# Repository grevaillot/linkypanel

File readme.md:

# linky2ble epaper panel

## Preview:

## Schematics:

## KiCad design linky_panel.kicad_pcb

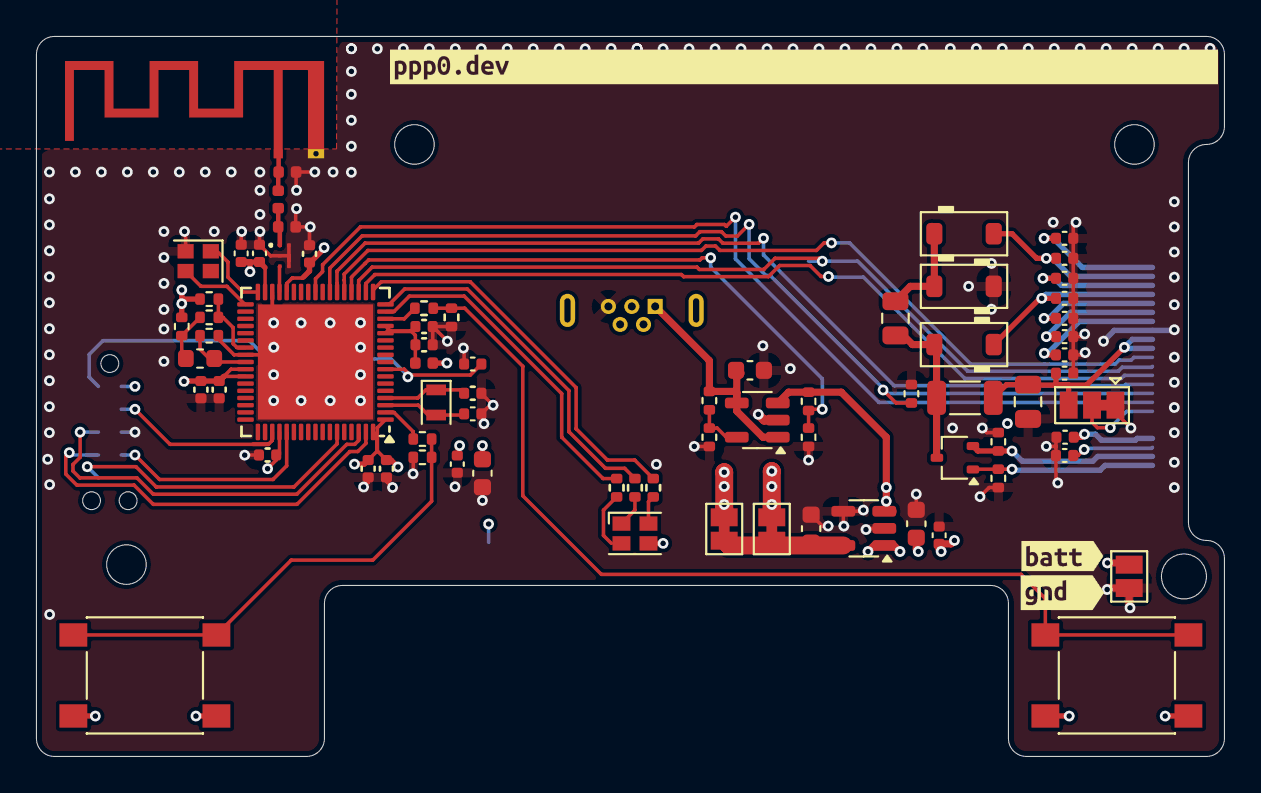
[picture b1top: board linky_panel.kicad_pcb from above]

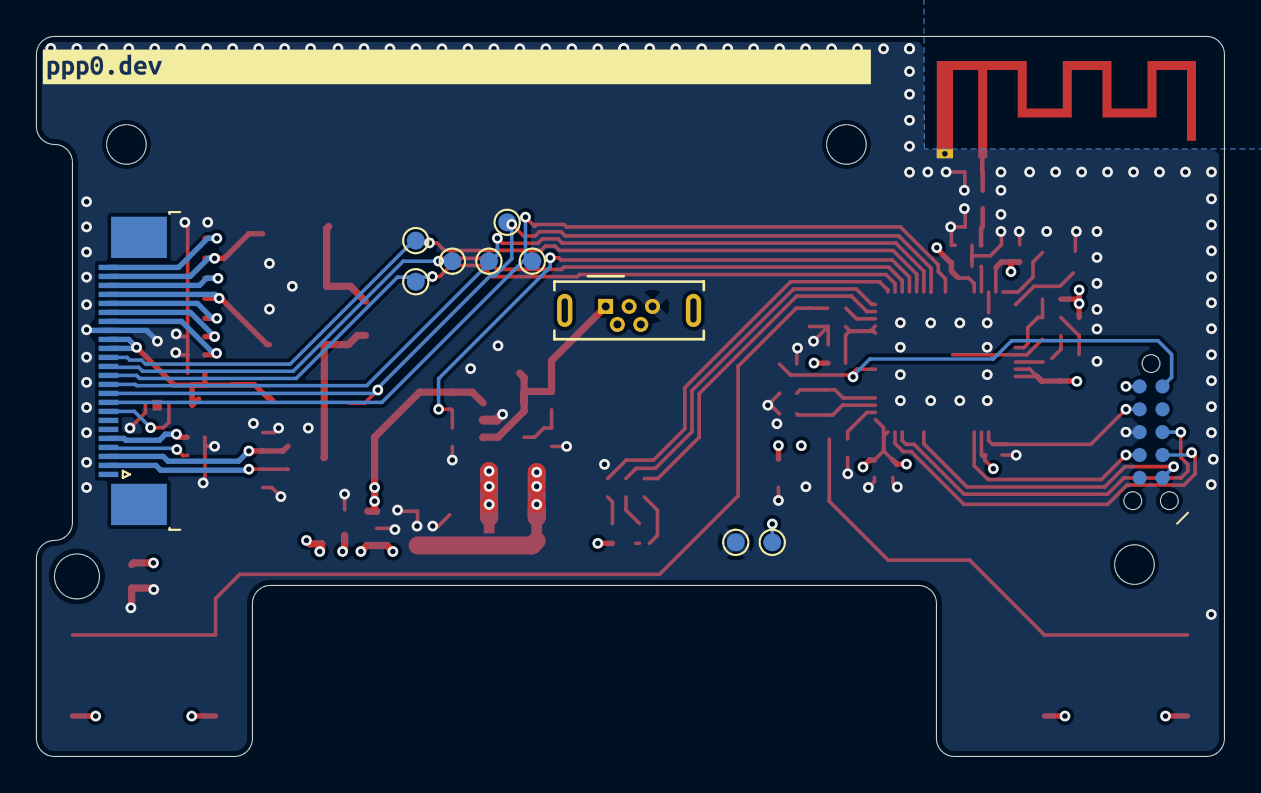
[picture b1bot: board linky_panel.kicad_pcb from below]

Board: 4 copper layers, 66.0 x 40.0 mm, 91 parts (12 on the bottom side), 55 nets.

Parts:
AE2: MLPF-WB55-01E3
AE3: Antenna; Texas_SWRA117D_2.4GHz_Left
C1, C2, C17, C33: 4.7uF; C_0603_1608Metric
C3, C5, C6, C9, C10, C11, C12, C13, C14, C16, C18, C27: 100nF; C_0402_1005Metric
C4: 100pF; C_0402_1005Metric
C7, C8: 10pF; C_0402_1005Metric
C15: 10nF; C_0402_1005Metric
C19, C20, C21, C22, C23, C24, C25, C28: 1uF; C_0402_1005Metric
C26: 1uF 25v; C_0402_1005Metric
C29, C30: 4.7uF 50V; C_0805_2012Metric
D1, D2, D3: MBR0530; D_SOD-123
D6: LED_RBAG; LED_Cree-PLCC4_2x2mm_CW
H1, H2, H2#2: MountingHole; MountingHole_2.2mm_M2
J1: Conn_01x24; TE_2-1734839-4_1x24-1MP_P0.5mm_Horizontal
J2: Conn_02x05_Counter_Clockwise; Tag-Connect_TC2050-IDC-NL_2x05_P1.27mm_Vertical
J3: USB_B_Micro; USB_Micro-B_Wuerth_614105150721_Vertical
J4: Conn_01x02_Pin; SolderJumper-2_P1.3mm_Open_Pad1.0x1.5mm
JP1: SolderJumper_3_Bridged123; SolderJumper-3_P1.3mm_Bridged12_Pad1.0x1.5mm
JP2, JP3: SolderJumper_2_Bridged; SolderJumper-2_P1.3mm_Bridged_Pad1.0x1.5mm
L1, L3: tbd; L_0402_1005Metric
L2, L4: 0; L_0402_1005Metric
L5: 1.8nH; L_0603_1608Metric
L6: 68uH; L_1206_3216Metric
Q1: Si1308EDL; SOT-323_SC-70
R1: 0,47; R_0402_1005Metric
R2, R3, R10, R11, R14, R15, R16: 0; R_0402_1005Metric
R4: 2.2; R_0402_1005Metric
R5, R6, R9: 1.5k; R_0402_1005Metric
R7, R8: 10k; R_0402_1005Metric
R12, R13: 100k; R_0402_1005Metric
R17: 220k; R_0402_1005Metric
R18: 470k; R_0402_1005Metric
SW1: SW1; SW_Push_1P1T_NO_6x6mm_H9.5mm
SW2: SW2; SW_Push_1P1T_NO_6x6mm_H9.5mm
TP1, TP2, TP3, TP4, TP5, TP6, TP7, TP8: 5v; TestPoint_Pad_D1.0mm
U1: TPS78230DDC; SOT-23-5
U2: MCP73811T-420I-OT; SOT-23-5
U3: STM32WB55RGVx; QFN-68-1EP_8x8mm_P0.4mm_EP6.4x6.4mm
Y1: nx2012 32.768khz; Crystal_SMD_2012-2Pin_2.0x1.2mm
Y2: NX2016SA 32.0Mhz EXS00A-CS06465; Crystal_SMD_2016-4Pin_2.0x1.6mm
kibuzzard-670FAF92, kibuzzard-670FAF92#2: G***; kibuzzard-670FAF92
kibuzzard-6710CDD1: G***; kibuzzard-6710CDD1
kibuzzard-6710CDDC: G***; kibuzzard-6710CDDC

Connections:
+3.3V: C1.1, JP2.1 (A), JP3.2 (B), U1.5 (OUT)
+BATT: C2.1, C3.1, J4.2, R17.2, U1.1 (IN), U1.3 (EN), U2.3 (VBAT)
/button1: R10.2, U3.15 (PA0)
/button2: R11.2, U3.2 (PC13)
/epaper/bs: J1.8, JP1.2 (C)
/epaper/gdr: J1.2, Q1.1 (G), R12.1
/epaper/rese: J1.3, Q1.2 (S), R1.1
/epaper/vcom: C19.1, J1.24
/epaper/vdd_lcd: C26.1, J1.18, JP3.1 (A)
/epaper/vddio: C27.1, C29.1, J1.15, J1.16, JP1.3 (B), L6.1
/epaper/vgh: C22.1, D1.1 (K), J1.21
/epaper/vgl: C20.1, D2.2 (A), J1.23
/epaper/vpp: C24.1, J1.19
/epaper/vsh1: C23.1, J1.20
/epaper/vsh2: C25.1, J1.5
/epaper/vsl: C21.1, J1.22
/epd_busy: J1.9, TP6.1, U3.26 (PC5)
/epd_clk: J1.13, TP3.1, U3.20 (PA5)
/epd_cs: J1.12, TP4.1, U3.19 (PA4)
/epd_dc: J1.11, TP5.1, U3.23 (PA8)
/epd_mosi: J1.14, TP2.1, U3.22 (PA7)
/epd_rst: J1.10, R13.2, TP7.1, U3.24 (PA9)
/led_b: R5.1, U3.18 (PA3)
/led_g: R6.1, U3.16 (PA1)
/led_r: R9.1, U3.17 (PA2)
/vbat_div: R17.1, R18.2, U3.21 (PA6)
/wb55/ant_path: AE2.1 (OUT), L2.2, L3.2
/wb55/pi_to_ant: AE3.1 (A), L1.2, L2.1
/wb55/rst: C5.1, J2.10, U3.8 (NRST)
/wb55/swclk: J2.4, U3.56 (PA14)
/wb55/swdio: J2.2, U3.54 (PA13)
/wb55/swo: J2.6, U3.63 (PB3)
/wb55/uart_rxd: J2.7, U3.67 (PB7)
/wb55/uart_txd: J2.8, U3.66 (PB6)
/wb55/vdda: C13.1, C15.1, L4.1, U3.13 (VREF+), U3.14 (VDDA)
GND: AE2.2 (GND4), AE2.4 (GND1), AE2.5 (GND2), AE2.6 (GND3), AE3.2 (gnd), C1.2, C2.2, C3.2, C4.2, C5.2, C6.2, C7.2, C8.2, C9.2, C10.2, C11.2, C12.2, C13.2, C14.2, C15.2, C16.2, C17.2, C18.2, C19.2, C20.2, C21.2, C22.2, C23.2, C24.2, C25.2, C26.2, C27.2, C28.2, C29.2, C33.2, D3.1 (K), J1.17, J2.3, J3.5 (GND), J4.1, JP1.1 (A), L1.1, L3.1, R1.2, R7.2, R8.2, R12.2, R13.1, R14.2, R15.2, R18.1, TP8.1, U1.2 (GND), U1.4 (GND), U2.2 (VSS), U3.32 (VSSRF), U3.42 (VSSSMPS), U3.69 (VSS), Y2.2
unnamed: AE2.3 (IN), U3.31 (RF1)
unnamed: C30.2, D1.2 (A), L6.2, Q1.3 (D)
unnamed: C30.1, D2.1 (K), D3.2 (A)
unnamed: D6.2 (BK), R5.2
unnamed: D6.4 (GK), R6.2
unnamed: D6.1 (RK), R9.2
unnamed: C28.1, J1.4
unnamed: L5.1, R3.2, R4.2
unnamed: R7.1, R10.1, SW1.1
unnamed: R8.1, R11.1, SW2.1
unnamed: R15.1, R16.2, U2.5 (PROG)
unnamed: U3.35 (OSC_IN), Y2.3
unnamed: U3.34 (OSC_OUT), Y2.1
unnamed: C7.1, U3.3 (PC14), Y1.2
unnamed: C8.1, U3.4 (PC15), Y1.1
unnamed: R2.2, R3.1, U3.41 (VFBSMPS)
unnamed: L5.2, R14.1, U3.43 (VLXSMPS)
VBUS: C33.1, J3.1 (VBUS), R16.1, U2.1 (CEN), U2.4 (VDD)
VDD: C4.1, C6.1, C9.1, C10.1, C11.1, C12.1, C14.1, C16.1, C17.1, C18.1, D6.3 (A), J2.1, JP2.2 (B), L4.2, R2.1, R4.1, SW1.2, SW2.2, TP1.1, U3.1 (VBAT), U3.30 (VDD), U3.33 (VDDRF), U3.44 (VDDSMPS), U3.45 (VDD), U3.55 (VDDUSB), U3.68 (VDD)

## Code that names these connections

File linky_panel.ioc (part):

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Mcu.Name=STM32WB55REVx
Mcu.Package=VFQFPN68
Mcu.UserName=STM32WB55REVx
PA0.Mode=SYS_WakeUp0
PA0.Signal=SYS_WKUP1
PA1.Signal=S_TIM2_CH2
PA13.Mode=Trace_Asynchronous_SW
PA13.Signal=SYS_JTMS-SWDIO
PA14.Mode=Trace_Asynchronous_SW
PA14.Signal=SYS_JTCK-SWCLK
PA2.Signal=S_TIM2_CH3
PA3.Signal=S_TIM2_CH4
PA4.Mode=NSS_Signal_Hard_Output
PA4.Signal=SPI1_NSS
PA5.Mode=TX_Only_Simplex_Unidirect_Master
PA5.Signal=SPI1_SCK
PA7.Mode=TX_Only_Simplex_Unidirect_Master
PA7.Signal=SPI1_MOSI
PB3.Mode=Trace_Asynchronous_SW
PB3.Signal=SYS_JTDO-SWO
PB6.Mode=Asynchronous
PB6.Signal=USART1_TX
PB7.Mode=Asynchronous
PB7.Signal=USART1_RX
PC13.Mode=SYS_WakeUp1
PC13.Signal=SYS_WKUP2
PC14-OSC32_IN.Mode=LSE-External-Oscillator
PC14-OSC32_IN.Signal=RCC_OSC32_IN
PC15-OSC32_OUT.Mode=LSE-External-Oscillator
PC15-OSC32_OUT.Signal=RCC_OSC32_OUT
PC5.Mode=SYS_WakeUp4
PC5.Signal=SYS_WKUP5
RCC.HSE_VALUE=32000000
RCC.SYSCLKFreq_VALUE=32000000
RCC.SYSCLKSource=RCC_SYSCLKSOURCE_HSE
board=custom

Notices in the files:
parts and their libraries:
Copyright 2021 Accelerated Designs. All rights reserved.
